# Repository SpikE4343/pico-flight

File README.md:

# pico-flight

# How To Build
 
 * Current two ways to build
  * For device RPi pico board
  * Tools
    * `PF_BUILD_TOOLS=ON`
 - [ ] Investigate using "target or platform" instead of custom variable
### Firmare for RP2040 (Pico)

```
mkdir builds
mkdir builds/firmware
cd builds/firmware
cmake ../..
make
```

### Tools
```
mkdir builds
mkdir builds/tools
cd builds/tools
cmake ../.. -D PF_BUILD_TOOLS=ON
make
```

## Plans
  - [ ] **PIO based on screen display**
    - [ ] Vertical and horizontal sync tracking of existing NTSC/PAL signal
    - [x] First steps to attempt to get simple "tvout" signal working, try starting from vga examples
    - [x] Minimum voltages required
       | Status | Voltage | Notes
       |--- | ---| --- |
       |  | NC | Not connected, leave existing signal intact|
       |  | 0V | sync level |
       |  | 1V | Black/Blanking  |
       |  | 3.3v | White |
    - [x] Still has some v-sync issues, probably from end of frame to start of next frame timing inconsistencies.
      - [x] Convert to chained dma transfer to automatically restart the frame.
        > Pacing timers only govern when an individual transfer happens, not the entire channel trigger
  - [ ] **PIO based camera stream**       
  - [ ] **Configuration Protocol**
    * Device maintains schema for transmition to configurator (any other device)
    * Key Value pairing treat like register map
    - [ ] Telemetry
    - [x] Add config data to telemetry
      - [x] Allow device to accept value mod messages to write to config data
      - [ ] Add littlefs for flash file storage
        - [ ] Read/Write to "file" all config vars
          - [x] Write of text based config vars 
        - [ ] Logging to flash/sdcard

    - [ ] Configurator
      - [ ] Native
        - [x] Openframeworks based via serial port with read/write support
          * OF dependency is pretty large and I lost the ofApp.cpp file :(
        - [x] Reimplementing using https://github.com/Immediate-Mode-UI/Nuklear and SDL/OpenGL
        - [x] Reimplemented using Dear Imgui
          - [ ] Debug why settings not applying on device when sent from tool
    - Web
      - [x] usb network endpoint
        - [x] basic http server 
        - [ ] route handling for subsystems
    - [ ] Host on device flash
      - [ ] Store current settings in human readable format.
      - [ ] Keep a backup of last settings?
    
## Pico Pinouts

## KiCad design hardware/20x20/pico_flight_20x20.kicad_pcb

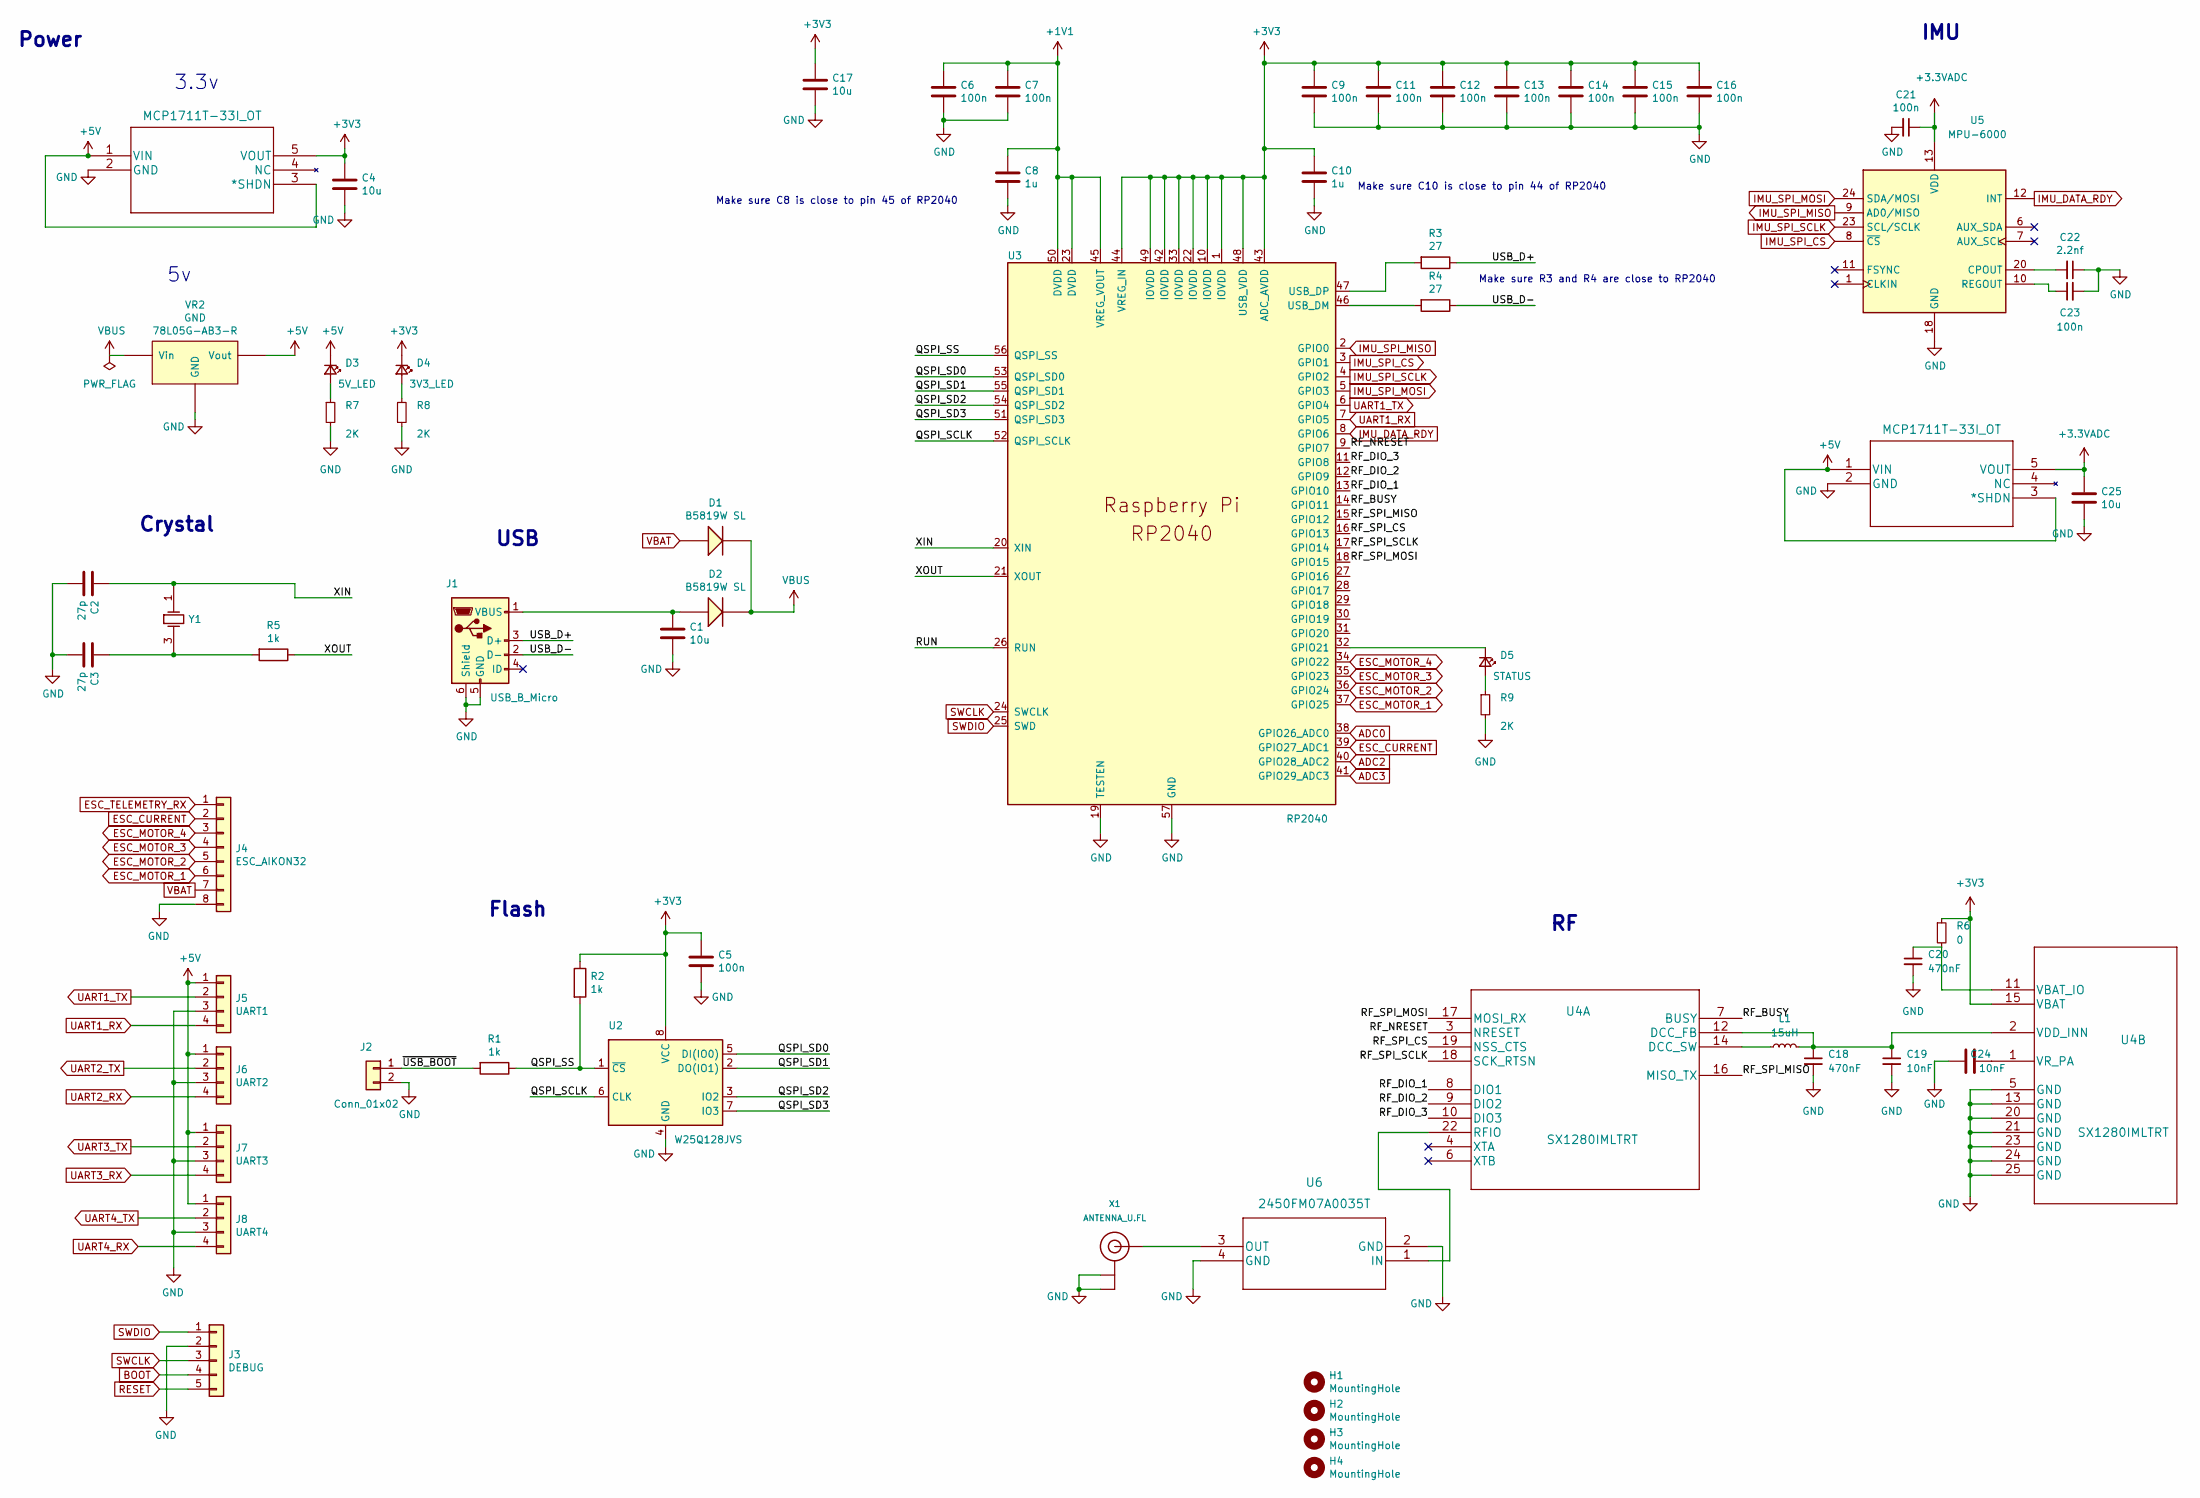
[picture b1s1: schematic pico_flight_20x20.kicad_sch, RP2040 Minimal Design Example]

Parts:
C1, C4, C17, C25: 10u; C_0603_1608Metric
C2, C3: 27p; C_0402_1005Metric
C5, C21, C23: 100n; C_0402_1005Metric
C6, C7, C9, C11, C12, C13, C14, C15, C16: 100n; C_0603_1608Metric
C8, C10: 1u; C_0603_1608Metric
C18, C20: 470nF; R_0402_1005Metric
C19: 10nF; R_0402_1005Metric
C22: 2.2nf; C_0402_1005Metric
C24: 10nF; C_0603_1608Metric
D1, D2: SOD-123_B5819W__SL; SOD-123
D3: 5V_LED; LED_0603_1608Metric
D4: 3V3_LED; LED_0603_1608Metric
D5: STATUS; LED_0603_1608Metric
H1, H2, H3, H4: MountingHole; MountingHole_4mm
J1: USB_B_Micro; USB_Micro-B_Amphenol_10103594-0001LF_Horizontal_modified
J2: Conn_01x02; PAD_X2_SMD_01x02
J3: DEBUG; PAD_X5_SMD_03x02
J4: ESC_AIKON32; JST_SHL_SM08B-SHLS-TF_1x08-1MP_P1.00mm_Horizontal
J5: UART1; PAD_X4_SMD_03x02
J6: UART2; PAD_X4_SMD_03x02
J7: UART3; PAD_X4_SMD_03x02
J8: UART4; PAD_X4_SMD_03x02
L1: 15uH; L_0603_1608Metric
R1, R2, R5: 1k; R_0402_1005Metric
R3, R4: 27; R_0402_1005Metric
R6: 0; R_0402_1005Metric
R7, R8, R9: 2K; R_0402_1005Metric
U1, U7: MCP1711T-33I_OT; SOT-23-5
U2: W25Q128JVS; SOIC-8_5.23x5.23mm_P1.27mm
U3: RP2040; RP2040-QFN-56
U4: SX1280IMLTRT
U5: MPU-6000; InvenSense_QFN-24_4x4mm_P0.5mm
U6: 2450FM07A0035T
VR2: SOT-89_78L05G-AB3-R; SOT-89(SOT-89-3)
X1: ANTENNA_U.FL; U.FL
Y1: SMD-3225_4P__12MHZ_20PF_10PPM; SMD-3225_4P

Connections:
+1V1: C6.1, C7.1, C8.1, U3.23 (DVDD), U3.45 (VREG_VOUT), U3.50 (DVDD)
+3.3VADC: C21.1, C25.1, U5.13 (VDD), U7.5 (VOUT)
+3V3: C4.1, C5.1, C9.1, C10.1, C11.1, C12.1, C13.1, C14.1, C15.1, C16.1, C17.1, D4.1 (K), R2.1, R6.1, U1.5 (VOUT), U2.8 (VCC), U3.1 (IOVDD), U3.10 (IOVDD), U3.22 (IOVDD), U3.33 (IOVDD), U3.42 (IOVDD), U3.43 (ADC_AVDD), U3.44 (VREG_IN), U3.48 (USB_VDD), U3.49 (IOVDD), U4.15 (VBAT)
+5V: D3.1 (K), J5.1, J6.1, J7.1, J8.1, U1.1 (VIN), U1.3 (*SHDN), U7.1 (VIN), U7.3 (*SHDN), VR2.1 (Vout)
/QSPI_SCLK: U2.6 (CLK), U3.52 (QSPI_SCLK)
/QSPI_SD0: U2.5 (DI(IO0)), U3.53 (QSPI_SD0)
/QSPI_SD1: U2.2 (DO(IO1)), U3.55 (QSPI_SD1)
/QSPI_SD2: U2.3 (IO2), U3.54 (QSPI_SD2)
/QSPI_SD3: U2.7 (IO3), U3.51 (QSPI_SD3)
/QSPI_SS: R1.1, R2.2, U2.1 (~CS), U3.56 (QSPI_SS)
/RF_BUSY: U3.14 (GPIO11), U4.7 (BUSY)
/RF_DIO_1: U3.13 (GPIO10), U4.8 (DIO1)
/RF_DIO_2: U3.12 (GPIO9), U4.9 (DIO2)
/RF_DIO_3: U3.11 (GPIO8), U4.10 (DIO3)
/RF_NRESET: U3.9 (GPIO7), U4.3 (NRESET)
/RF_SPI_CS: U3.16 (GPIO13), U4.19 (NSS_CTS)
/RF_SPI_MISO: U3.15 (GPIO12), U4.16 (MISO_TX)
/RF_SPI_MOSI: U3.18 (GPIO15), U4.17 (MOSI_RX)
/RF_SPI_SCLK: U3.17 (GPIO14), U4.18 (SCK_RTSN)
/RUN: U3.26 (RUN)
/USB_D+: J1.3 (D+), R3.1
/USB_D-: J1.2 (D-), R4.1
/XIN: C2.1, U3.20 (XIN), Y1.1 (OSC1)
/XOUT: R5.1, U3.21 (XOUT)
/~USB_BOOT: J2.1, R1.2
ADC0: U3.38 (GPIO26_ADC0)
ADC2: U3.40 (GPIO28_ADC2)
ADC3: U3.41 (GPIO29_ADC3)
BOOT: J3.4
ESC_CURRENT: J4.2, U3.39 (GPIO27_ADC1)
ESC_MOTOR_1: J4.6, U3.37 (GPIO25)
ESC_MOTOR_2: J4.5, U3.36 (GPIO24)
ESC_MOTOR_3: J4.4, U3.35 (GPIO23)
ESC_MOTOR_4: J4.3, U3.34 (GPIO22)
ESC_TELEMETRY_RX: J4.1
GND: C1.2, C2.2, C3.2, C4.2, C5.2, C6.2, C7.2, C8.2, C9.2, C10.2, C11.2, C12.2, C13.2, C14.2, C15.2, C16.2, C17.2, C18.2, C19.2, C20.2, C21.2, C22.1, C23.2, C24.1, C25.2, J1.5 (GND), J1.6 (Shield), J2.2, J3.2, J4.8, J5.3, J6.3, J7.3, J8.3, R7.2, R8.2, R9.2, U1.2 (GND), U2.4 (GND), U3.19 (TESTEN), U3.57 (GND), U4.5 (GND), U4.13 (GND), U4.20 (GND), U4.21 (GND), U4.23 (GND), U4.24 (GND), U4.25 (GND), U5.18 (GND), U6.2 (GND), U6.4 (GND), U7.2 (GND), VR2.2 (GND), X1.1 (GND@0), X1.2 (GND@1)
IMU_DATA_RDY: U3.8 (GPIO6), U5.12 (INT)
IMU_SPI_CS: U3.3 (GPIO1), U5.8 (~CS)
IMU_SPI_MISO: U3.2 (GPIO0), U5.9 (AD0/MISO)
IMU_SPI_MOSI: U3.5 (GPIO3), U5.24 (SDA/MOSI)
IMU_SPI_SCLK: U3.4 (GPIO2), U5.23 (SCL/SCLK)
unnamed: C1.1, D2.1 (A), J1.1 (VBUS)
unnamed: C3.1, R5.2, Y1.3 (OSC2)
unnamed: C18.1, C19.1, L1.2, U4.2 (VDD_INN), U4.12 (DCC_FB)
unnamed: C20.1, R6.2, U4.11 (VBAT_IO)
unnamed: C22.2, U5.20 (CPOUT)
unnamed: C23.1, U5.10 (REGOUT)
unnamed: C24.2, U4.1 (VR_PA)
unnamed: D3.2 (A), R7.1
unnamed: D4.2 (A), R8.1
unnamed: D5.1 (K), U3.32 (GPIO21)
unnamed: D5.2 (A), R9.1
unnamed: L1.1, U4.14 (DCC_SW)
unnamed: R3.2, U3.47 (USB_DP)
unnamed: R4.2, U3.46 (USB_DM)
unnamed: U4.22 (RFIO), U6.1 (IN)
unnamed: U6.3 (OUT), X1.3 (SIGNAL)
RESET: J3.5
SWCLK: J3.3, U3.24 (SWCLK)
SWDIO: J3.1, U3.25 (SWD)
UART1_RX: J5.4, U3.7 (GPIO5)
UART1_TX: J5.2, U3.6 (GPIO4)
UART2_RX: J6.4
UART2_TX: J6.2
UART3_RX: J7.4
UART3_TX: J7.2
UART4_RX: J8.4
UART4_TX: J8.2
VBAT: D1.1 (A), J4.7
VBUS: D1.2 (K), D2.2 (K), VR2.3 (Vin)

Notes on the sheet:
Power
Crystal
Flash
IMU
Make sure C8 is close to pin 45 of RP2040
USB
Make sure C10 is close to pin 44 of RP2040
3.3v
Make sure R3 and R4 are close to RP2040

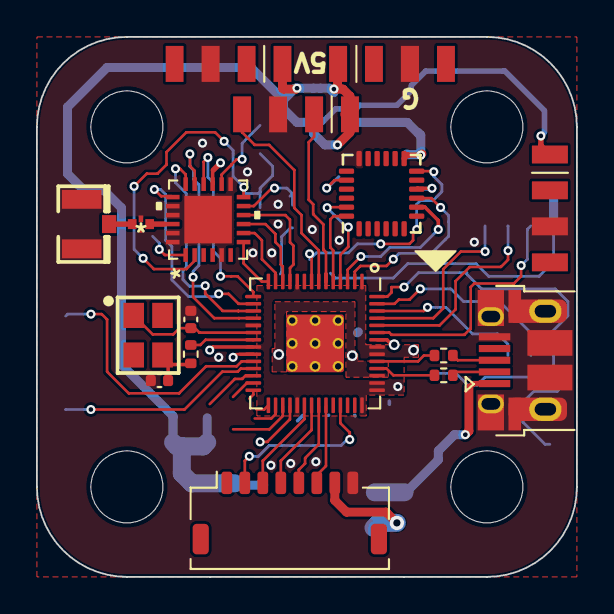
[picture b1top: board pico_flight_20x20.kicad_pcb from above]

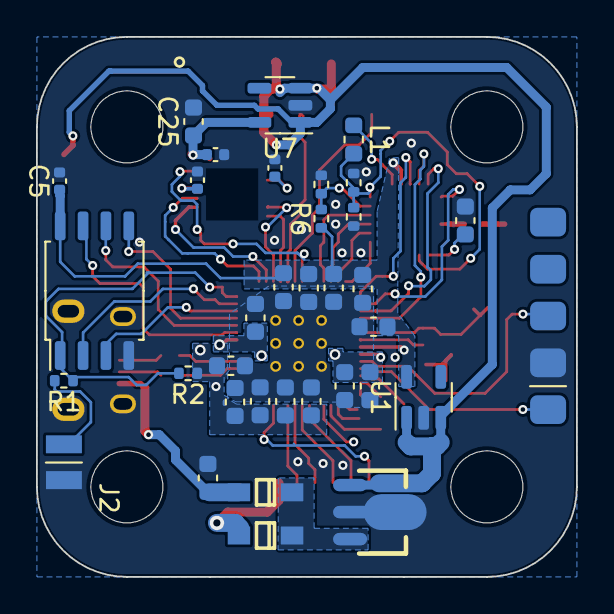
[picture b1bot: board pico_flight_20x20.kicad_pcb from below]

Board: 2 copper layers, 30.0 x 30.0 mm, 56 parts (35 on the bottom side), 53 nets.

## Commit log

2021-05-01 Initial import - WIP not compiling
2021-05-01 Remove stray binary file
2021-05-01 :WIP: adding data vars for gyro. Change data var value interface from value -> v
2021-05-02 WIP:motor mixer data var setup
2021-05-02 WIP: refactor of config structs to data vars. compiles now but not linking yet....
2021-05-04 config data refactor seems to be working now
2021-05-04 Add value sample with send of value desc
2021-05-04 Latest Updates
2021-05-25 colletor tool refactor to parse header and payload data first, then pass to construct
2021-05-26 device reading telemetry data var write mods from collector
2021-05-26 Telemetry: Use data_type enum mapping so data value is set to the correct type
2021-05-27 add motor output calculation. Add floating point and negative value support to collector
2021-05-28 PID attitude control with data vars
2021-06-19 Fix dshot packet crc to not include 4 least significant bits of full packet, to match betaflight code. Refactor to start to remove native code from common code. Add system library with time function 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
2021-06-29 Add rc rx dma support. Add usb rndis (thanks to pico_stuff library) support with lwip based basic http server. Isolate io_rc code for protocols
2021-06-29 Readme and submodule cleanup
2021-07-10 Motor control clean up. Change tv-out to chained dma channels to remove post frame delay and stabilize image
2021-07-10 Add openframeworks based configuration and telemetry tool
2021-07-10 Update docs
2021-11-24 Allow usage of firmware libraries in tools
2021-11-29 Build telemetry for collector mode, and POC with new ui library
2021-11-30 Migrate to imgui for gui tool
2021-12-05 Add serial stream recording and playback to telemetry tool. Tool can also dump to text file the current set of data vars
2021-12-09 Fix configurator sending invalid telemetry messages. Add kicad files for 20x20 pcb
2021-12-15 Add implot, test mahi-gui, progress on pcb
2021-12-16 45 degree layout
2021-12-22 Add basic mpu6000 gyro support. Needs it's own driver still
2021-12-23 latest board
2022-01-02 Update to kicad 6 more progress on 20x20 board layout
2022-01-15 Latest work on perfboard
2022-01-15 latest kicad files
2022-01-17 Get rx uart working again as well as telemetry sending again. Seems to be some issue with alarm timers that stopped call print task
2022-03-02 Work to track down output stall. Tracked down dma overwrite, but still stalls

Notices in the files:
parts and their libraries:
Copyright 2021 Accelerated Designs. All rights reserved.
